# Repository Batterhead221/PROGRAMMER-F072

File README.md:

* TypeC-Debugger-F072 (DEBUGGER_V1.0)

USB-C (USB 2.0) STM32F072CBT6-based programmer/debug adapter board.

> Project status: Prototype

## What it does
- USB-C powered + USB 2.0 device interface
- Target programming/debug via **SWD**
- Dedicated reset control and debug access points
- On-board power section (labeled **POWER**) with switching and protection components

## Hardware overview
- MCU: **STM32F072CBT6**
- USB: **USB-C 2.0** (device/UFP configuration)
- Debug: **SWDIO / SWCLK / NRST / GND**
- Board: **DEBUGGER_V1.0**

## Connectors & headers
- **USB-C**: primary power + USB data connection
- **J2 (DEBUG header)**: main target interface header (SWD + reset + power reference)
- **J1 / J3 / S1 / S2**: board configuration/jumper/select features (see silkscreen)

## Test points (silkscreen labels)
- **TP2_3V3**: 3.3V rail test point
- **TP3_GND**: ground reference test point
- **TP4_NRST**: target reset test point
- **TP5_SWDIO**: SWD data test point
- **TP6_SWCLK**: SWD clock test point

## On-board power (POWER block)
Located on the left side of the board (near **SW1** and components marked U3/U4).
- Input comes from USB-C 5V
- Generates and distributes rails used by the MCU/debug interface
- Protection/fusing present (F1)

## Buttons / switches
- **RESET area (SW2)**: reset functionality (see silkscreen)
- **SW1 (POWER area)**: power-related switching (see silkscreen)

## Bring-up checklist
1. Inspect for shorts around USB-C, power, and the MCU.
2. Plug in USB-C and confirm:
   - **TP2_3V3** reads ~3.3V
   - **TP3_GND** is solid ground reference
3. Confirm reset behavior at **TP4_NRST**.
4. Verify SWD signals at **TP5_SWDIO** and **TP6_SWCLK**.
5. Connect target to **J2** and attempt SWD connection with your chosen firmware/protocol.

## Repo structure
- `hardware/` KiCad project, footprints, outputs
- `firmware/` programmer/debug firmware (protocol TBD)
- `images/` renders and board photos

## Notes
- This board is intended as a compact USB-C SWD debugger platform.
- Protocol/compatibility target (CMSIS-DAP, ST-Link-like, custom) is a firmware decision.

* BRINGUP.md (DEBUGGER_V1.0)

# Bring-up checklist for USB-C STM32F072 debugger board.

## Tools
- USB-C cable + host PC
- DMM (multimeter)
- Optional: USB power meter, bench supply w/ current limit, scope
- Optional: ST-Link or another known-good SWD debugger (for cross-checking target header wiring)

## Safety / first power-on setup
- If you have a bench supply: set **5.0V** with **current limit = 0.10A** (then raise later).
- If powering from USB: a USB power meter is helpful to spot obvious shorts (current spike).

## 1) Visual inspection (unpowered)
- Check component orientation: MCU, diode/LED, polarized caps (if any), USB-C connector.
- Look for solder bridges around:
  - STM32 pins
  - USB-C pins
  - Any fine-pitch parts near USB
- Verify the fuse (F1) is present and looks properly soldered.

## 2) Quick resistance checks (unpowered)
Using DMM ohms/continuity:
- **5V (VBUS) to GND**: should NOT be a short.
- **3V3 to GND** (TP2_3V3 to TP3_GND): should NOT be a short.
- If either reads near 0Ω, stop and inspect.

## 3) First power-on (power only)
Power the board from USB-C (or bench 5V if you have a safe injection point).

### Measure rails
- Measure **TP2_3V3 → TP3_GND**
  - Expected: **~3.3V**
- Measure any labeled VIN/VBUS node (if you have a test point) to GND
  - Expected: **~5.0V**

## 4) Reset line check
- Measure **TP4_NRST** relative to GND.
  - Expected: typically **high** (near 3.3V) when not pressed.
  - When reset is asserted (button/switch): should pull **low**.

## 5) USB enumeration check (data path)
Plug into a PC and verify the device shows up.
- macOS: System Information → USB
- Windows: Device Manager
- Linux: `lsusb`

Expected outcome (pre-firmware): may enumerate only if boot firmware/config supports it.
If it does NOT enumerate yet, that’s OK at this stage. Confirm 3V3 first.

## 6) SWD header continuity sanity (J2)
J2 pinout reference:
- Pin 1: +3V3
- Pin 2: SWDIO
- Pin 3: GND
- Pin 4: SWCLK
- Pin 5: GND
- Pin 10: NRST

Continuity checks (unpowered):
- J2 GND pins → TP3_GND should beep.
- J2 +3V3 (Pin 1) → TP2_3V3 should beep.
- J2 NRST (Pin 10) → TP4_NRST should beep.

## 7) Firmware bring-up (later)
Not implemented yet. The board is still in transit and firmware work will start after first power-on validation.
Planned direction: **CMSIS-DAP** (subject to change).

## Tools
- USB-C cable + host PC
- DMM (multimeter)
- Optional: USB power meter, bench supply w/ current limit, scope
- Optional: ST-Link or another known-good SWD debugger (for cross-checking target header wiring)

## Safety / first power-on setup
- If you have a bench supply: set **5.0V** with **current limit = 0.10A** (then raise later).
- If powering from USB: a USB power meter is helpful to spot obvious shorts (current spike).

## 1) Visual inspection (unpowered)
- Check component orientation: MCU, diode/LED, polarized caps (if any), USB-C connector.
- Look for solder bridges around:
  - STM32 pins
  - USB-C pins
  - Any fine-pitch parts near USB
- Verify the fuse (F1) is present and looks properly soldered.

## 2) Quick resistance checks (unpowered)
Using DMM ohms/continuity:
- **5V (VBUS) to GND**: should NOT be a short.
- **3V3 to GND** (TP2_3V3 to TP3_GND): should NOT be a short.
- If either reads near 0Ω, stop and inspect.

## 3) First power-on (power only)
Power the board from USB-C (or bench 5V if you have a safe injection point).

### Measure rails
- Measure **TP2_3V3 → TP3_GND**
  - Expected: **~3.3V**
- Measure any labeled VIN/VBUS node (if you have a test point) to GND
  - Expected: **~5.0V**

## 4) Reset line check
- Measure **TP4_NRST** relative to GND.
  - Expected: typically **high** (near 3.3V) when not pressed.
  - When reset is asserted (button/switch): should pull **low**.

## 5) USB enumeration check (data path)
Plug into a PC and verify the device shows up.
- macOS: System Information → USB
- Windows: Device Manager
- Linux: `lsusb`

Expected outcome (pre-firmware): may enumerate only if boot firmware/config supports it.
If it does NOT enumerate yet, that’s OK at this stage. Confirm 3V3 first.

## 6) SWD header continuity sanity (J2)
J2 pinout reference:
- Pin 1: +3V3
- Pin 2: SWDIO
- Pin 3: GND
- Pin 4: SWCLK
- Pin 5: GND
- Pin 10: NRST

Continuity checks (unpowered):
- J2 GND pins → TP3_GND should beep.
- J2 +3V3 (Pin 1) → TP2_3V3 should beep.
- J2 NRST (Pin 10) → TP4_NRST should beep.

## 7) Firmware bring-up (later)
Once hardware passes power + reset checks:
- Decide firmware direction (likely **CMSIS-DAP**)
- Confirm USB stack + clock config
- Validate SWD IO toggling on TP5_SWDIO / TP6_SWCLK
- Attempt a target attach via J2

## If something fails
- 3V3 missing: check regulator/power section, fuse, and shorts on 3V3 rail.
- 3V3 present but no USB enumerate: check CC resistors/config, D+/D- routing, ESD parts, USB connector soldering.
- Reset stuck low: check pull-ups, reset switch wiring, NRST net shorts.
- High current draw: inspect for solder bridges, reversed parts, or incorrect footprints.

## Notes log
Date:
Observations:
Fixes tried:

Open ibom.html to view the interactive BOM and highlighted placement.

Engineered and Designed by Brandon Shelly

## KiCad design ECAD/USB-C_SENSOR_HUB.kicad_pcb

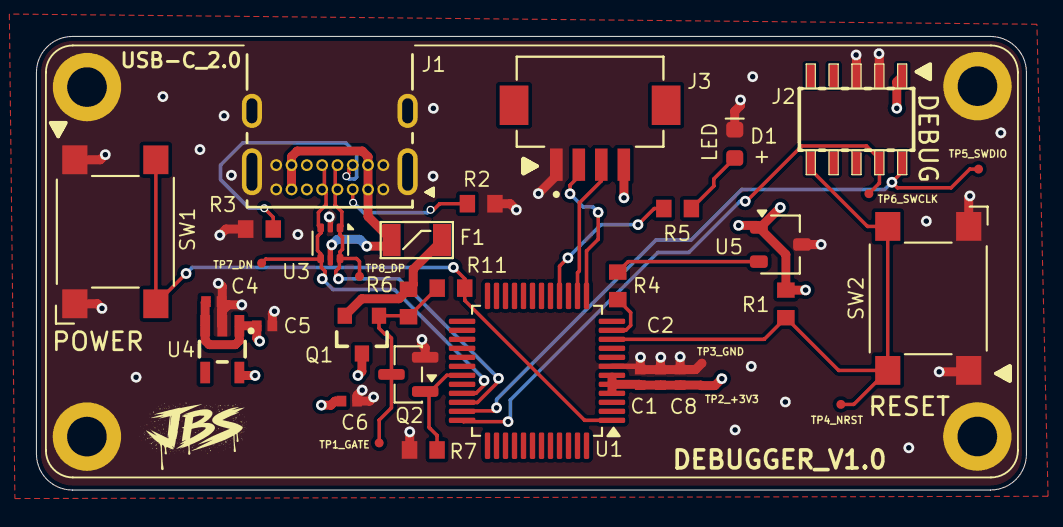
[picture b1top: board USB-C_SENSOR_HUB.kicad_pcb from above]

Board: 4 copper layers, 55.0 x 25.2 mm, 38 parts (0 on the bottom side), 21 nets.

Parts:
C1, C5, C6: 1UF; CAPC1005X55N
C2, C8: 100NF; CAPC1005X55N
C4: 0.1UF; CAPC1005X55N
D1: LED; LED_0603_1608Metric
F1: POLYFUSE; PTC-1206
J1: USB_C_Receptacle; CONN16_USB4085-GF-A_GCT
J2: CORTEX_DEBUGSMD; SAMTECH_FTSH-105-01
J3: DF13A-4P-1.25H_21_; HRS_DF13A-4P-1.25H_21_
MH: (no value)
MH#2, MH#3: (no value)
Q1: P-MOS; SOT23-3
Q2: N-MOS; SOT-23
R1, R4: 10K^; RESC1508X50N
R2, R3: 5.1K; RESC1508X50N
R5: 330; RESC1508X50N
R6, R7: 100K; RESC1508X50N
R11: 110; RESC1508X50N
SW1, SW2: SW_Push; SW_SPST_Omron_B3FS-101xP
TP1_GATE, TP2_+3V3, TP3_GND, TP4_NRST, TP5_SWDIO, TP6_SWCLK, TP7_DN, TP8_DP: 0.5mm; TestPoint-0.5mm
U1: STM32; LQFP-48_7x7mm_P0.5mm
U3: USBLC6-2P6; SOT-666
U4: V-REG; SOT23-5
U5: HALL_FX; SOT-23W

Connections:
/+3V3: C1.1, C2.1, C6.1, C8.1, J2.1 (VCC), J3.4, R1.1, TP2_+3V3.1, U1.4 (VBAT), U1.5 (VREF+), U1.6 (VDD), U4.5 (VOUT), U5.1 (V_{CC})
/CC1: J1.A5 (3), R2.2
/CC2: J1.B5 (14), R3.2
/HALL_OUT: R4.2, U1.11 (PA0)
/LED_STATUS: R5.2, U1.16 (PA5)
/NRST: J2.10 (NRESET), R1.2, SW2.2, TP4_NRST.1, U1.10 (PF2)
/PWR_BTN: R11.1, SW1.2, U1.1 (PC13)
/PWR_GATE: Q1.1 (G), Q2.3 (C), R6.1, R11.2, TP1_GATE.1
/PWR_HOLD: Q2.1 (B), R7.1, U1.31 (PC7)
/RAW_IN: F1.2, Q1.2 (S), R6.2
/SWCLK: J2.4 (SWDCLK/TCK), TP6_SWCLK.1, U1.36 (PA14)
/SWDIO: J2.2 (SWDIO/TMS), TP5_SWDIO.1, U1.35 (PA13)
/UART_RX: J3.3, U1.14 (PA3)
/UART_TX: J3.2, U1.13 (PA2)
/USB_N: J1.A7 (5), J1.B7 (12), TP7_DN.1, U1.33 (PA9/PA11), U3.3 (I/O2), U3.4 (I/O2)
/USB_P: J1.A6 (4), J1.B6 (13), TP8_DP.1, U1.34 (PA10/PA12), U3.1 (I/O1), U3.6 (I/O1)
/VBUS: F1.1, J1.A4 (2), J1.A9 (7), J1.B4 (15), J1.B9 (10), U3.5 (VBUS)
/VIN_SYS: C4.1, C5.1, Q1.3 (D), U4.1 (VIN), U4.3 (EN)
GND: C1.2, C2.2, C4.2, C5.2, C6.2, C8.2, D1.1 (K), J1.A1 (1), J1.A12 (8), J1.B1 (16), J1.B12 (9), J1.S1 (SHIELD), J2.3 (GND), J2.5 (GND), J3.1, MH.1, MH#2.1, MH#3.1, Q2.2 (E), R2.1, R3.1, R7.2, SW1.1, SW2.1, TP3_GND.1, U1.7 (VSS), U3.2 (GND), U4.2 (GND), U5.3 (GND)
unnamed: D1.2 (A), R5.1
unnamed: R4.1, U5.2 (V_{OUT})

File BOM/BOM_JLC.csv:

COMMENT,DESIGNATOR,FOOTPRINT,JLCPCB PART#
1UF,C1,GRM155R71C104KA88D:CAPC1005X55N,GRT155R61A105KE01D
1UF,C5,GRM155R71C104KA88D:CAPC1005X55N,GRT155R61A105KE01D
1UF,C6,GRM155R71C104KA88D:CAPC1005X55N,GRT155R61A105KE01D
100NF,C2,GRM155R71C104KA88D:CAPC1005X55N,GRM155R71H104KE14D
100NF,C4,GRM155R71C104KA88D:CAPC1005X55N,GRM155R71H104KE14D
100NF,C8,GRM155R71C104KA88D:CAPC1005X55N,GRM155R71H104KE14D
LED,D1,SparkFun-LED:LED_0603_1608Metric,LTST-C190KGKT
POLYFUSE,F1,SparkFun-PowerIC:PTC-1206,MF-NSMF050-2
DF13A-4P-1.25H_21_,J3,DF13A-4P-1:HRS_DF13A-4P-1.25H_21_,DF13A-4P-1.25H(21)
"P-MOSFET transistor, drain/gate/source",Q1,SparkFun-Semiconductor-Standard:SOT23-3,AO3407A
"0.2A Ic, 40V Vce, Small Signal NPN Transistor, SOT-23",Q2,Package_TO_SOT_SMD:SOT-23,AO3400A
10K,R1,CRCW060310K0FKEA:RESC1508X50N,RC0603FR-0710KL
10K,R4,CRCW060310K0FKEA:RESC1508X50N,RC0603FR-0710KL
5.1K,R2,CRCW060310K0FKEA:RESC1508X50N,RC0603FR-075K1L
5.1K,R3,CRCW060310K0FKEA:RESC1508X50N,RC0603FR-075K1L
330,R5,CRCW060310K0FKEA:RESC1508X50N,RC0603FR-07330RL
100K,R6,CRCW060310K0FKEA:RESC1508X50N,RC0603FR-07100KL
100K,R7,CRCW060310K0FKEA:RESC1508X50N,RC0603FR-07100KL
110,R11,CRCW060310K0FKEA:RESC1508X50N,RC0603FR-07110RL
STM32,U1,Package_QFP:LQFP-48_7x7mm_P0.5mm,STM32F072CBT6
USBLC6-2P6,U3,Package_TO_SOT_SMD:SOT-666,USBLC6-2P6
"600mA low dropout linear regulator, with enable pin, 3.8V-6V input voltage range, 3.3V fixed positive output, SOT-23-5",U4,SparkFun-Semiconductor-Standard:SOT23-5,AP2112K-3.3TRG1
"Hall effect switch, unipolar (south-polarity), Bop=70-350G, Brp=50-330G, 3.8-24V supply, SOT-23W",U5,Package_TO_SOT_SMD:SOT-23W,AH1806-W-7

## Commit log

2026-03-03 UPDATE
    UPDATE
2026-03-03 PUSH
    PUSH
